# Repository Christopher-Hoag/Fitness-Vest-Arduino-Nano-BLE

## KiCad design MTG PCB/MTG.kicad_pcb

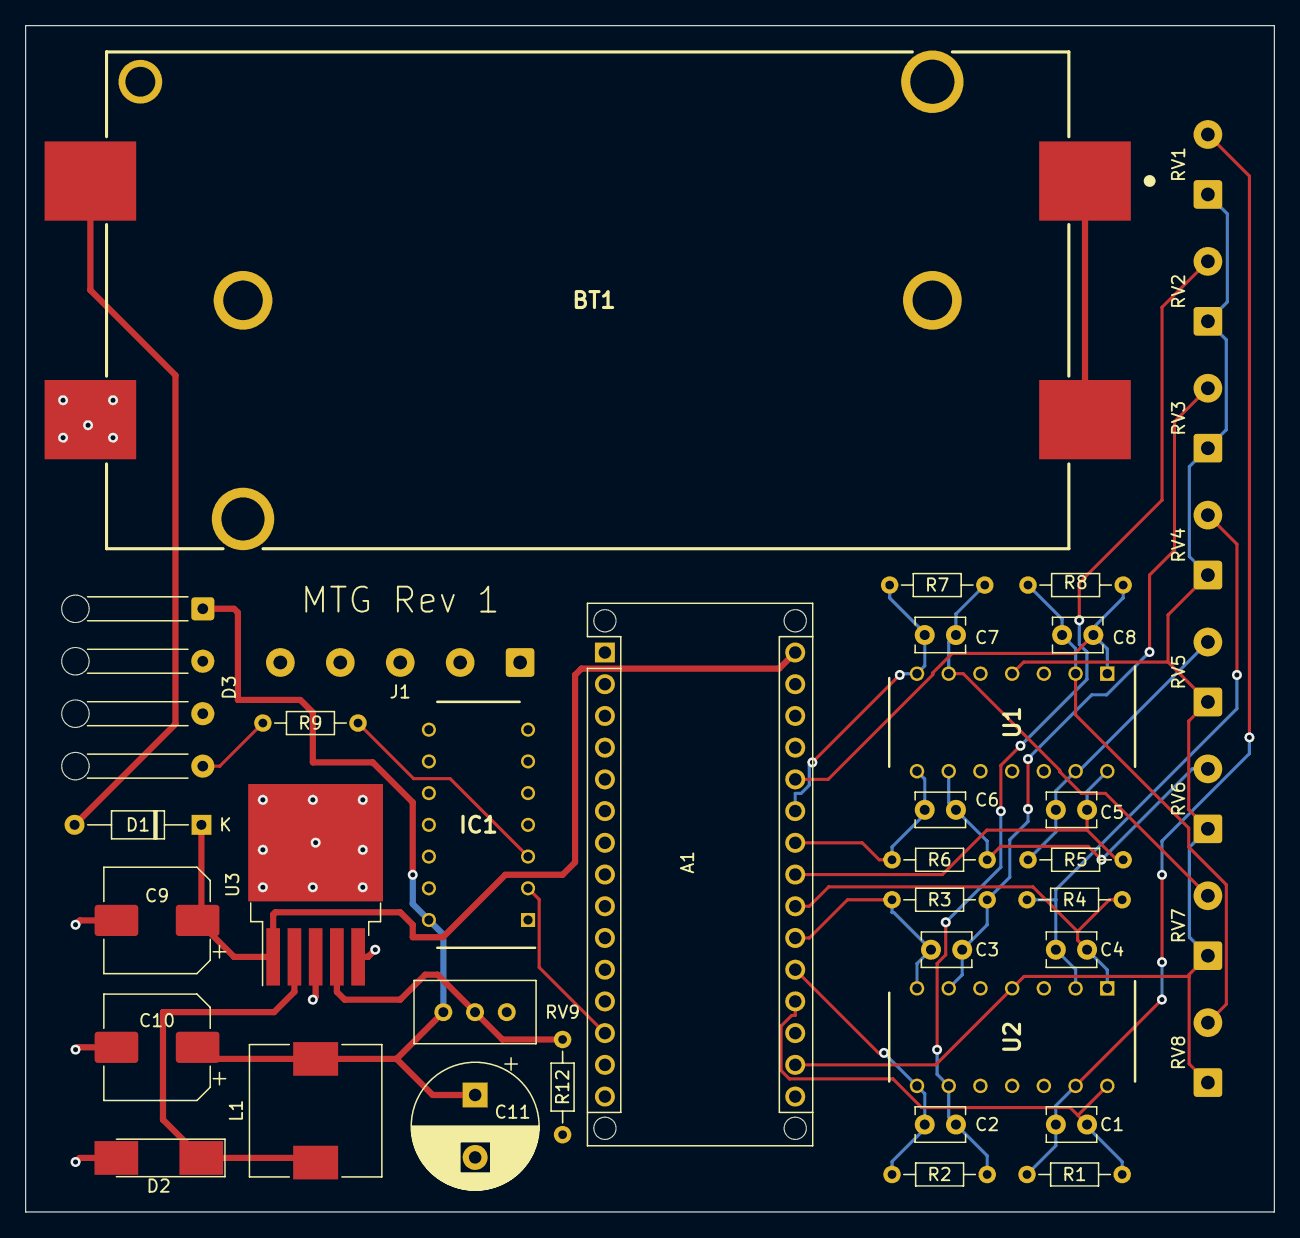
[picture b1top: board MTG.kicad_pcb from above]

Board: 2 copper layers, 100.0 x 95.0 mm, 41 parts (0 on the bottom side), 26 nets.

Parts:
A1: Arduino_Nano_33_BLE; Arduino_Nano_WithMountingHoles
BT1: 4.5-21V; 1048
C1, C2, C3, C4, C5, C6, C7, C8: 47pF; C_Disc_D3.8mm_W2.6mm_P2.50mm
C9: 100u; CP_Elec_8x10
C10: 220u; CP_Elec_8x10
C11: 1000u; CP_Radial_D10.0mm_P5.00mm
D1: SB120; D_DO-35_SOD27_P10.16mm_Horizontal
D2: SS34; D_MELF_Handsoldering
D3: NeoPixel V2; SolderWire-0.25sqmm_1x04_P4.2mm_D0.65mm_OD1.7mm_Relief
IC1: SN74AHCT125N; DIP794W53P254L1930H508Q14N
J1: PIM438; SolderWire-0.5sqmm_1x05_P4.8mm_D0.9mm_OD2.3mm
L1: 47u; L_10.4x10.4_H4.8
R1, R2, R3, R4, R5, R6, R7, R8, R12: 1K; R_Axial_DIN0204_L3.6mm_D1.6mm_P7.62mm_Horizontal
R9: ~200-400; R_Axial_DIN0204_L3.6mm_D1.6mm_P7.62mm_Horizontal
RV1, RV2, RV3, RV4, RV5, RV6, RV7, RV8: FSR01CE; SolderWire-0.5sqmm_1x02_P4.8mm_D0.9mm_OD2.3mm
RV9: R_Potentiometer_Trim; Potentiometer_Bourns_3296W_Vertical
U1, U2: MCP6004; DIP781W56P254L1918H533Q14N
U3: LM2596S-ADJ; TO-263-5_TabPin3

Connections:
+3.3V: A1.17 (3V3), RV1.1, RV2.1, RV3.1, RV4.1, RV5.1, RV6.1, RV7.1, RV8.1, U1.4 (V+), U2.4 (V+)
+5V: C10.1, C11.1, D3.1 (VDD), IC1.14 (VCC), L1.2, RV9.1
GND: A1.4 (GND), A1.29 (GND), BT1.2 (-), C9.2, C10.2, C11.2, D2.2 (A), D3.3 (VSS), IC1.7 (GND), J1.1, R12.1, U1.3 (+), U1.5 (+), U1.10 (+), U1.11 (V-), U1.12 (+), U2.3 (+), U2.5 (+), U2.10 (+), U2.11 (V-), U2.12 (+), U3.3 (GND), U3.5 (~ON/OFF)
unnamed: A1.13 (D10), IC1.2 (1A)
unnamed: A1.19 (A0), C1.1, R1.2, U2.14
unnamed: A1.20 (A1), C2.1, R2.2, U2.8
unnamed: A1.21 (A2), C3.1, R3.2, U2.7
unnamed: A1.22 (A3), C4.1, R4.2, U2.1
unnamed: A1.23 (A4), C5.1, R5.2, U1.14
unnamed: A1.24 (A5), C6.1, R6.2, U1.8
unnamed: A1.25 (A6), C7.1, R7.2, U1.7
unnamed: A1.26 (A7), C8.1, R8.2, U1.1
unnamed: A1.30 (VIN), C9.1, D1.1 (K), U3.1 (VIN)
unnamed: BT1.1 (+), D1.2 (A)
unnamed: C1.2, R1.1, RV1.2, U2.13 (-)
unnamed: C2.2, R2.1, RV2.2, U2.9 (-)
unnamed: C3.2, R3.1, RV3.2, U2.6 (-)
unnamed: C4.2, R4.1, RV4.2, U2.2 (-)
unnamed: C5.2, R5.1, RV5.2, U1.13 (-)
unnamed: C6.2, R6.1, RV6.2, U1.9 (-)
unnamed: C7.2, R7.1, RV7.2, U1.6 (-)
unnamed: C8.2, R8.1, RV8.2, U1.2 (-)
unnamed: D2.1 (K), L1.1, U3.2 (OUT)
unnamed: D3.4 (DIN), R9.1
unnamed: IC1.3 (1Y), R9.2
unnamed: R12.2, RV9.2, U3.4 (FB)

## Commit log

2023-02-08 Main
2023-07-20 Add files via upload
    KiCAD PCB design files for MTG.
